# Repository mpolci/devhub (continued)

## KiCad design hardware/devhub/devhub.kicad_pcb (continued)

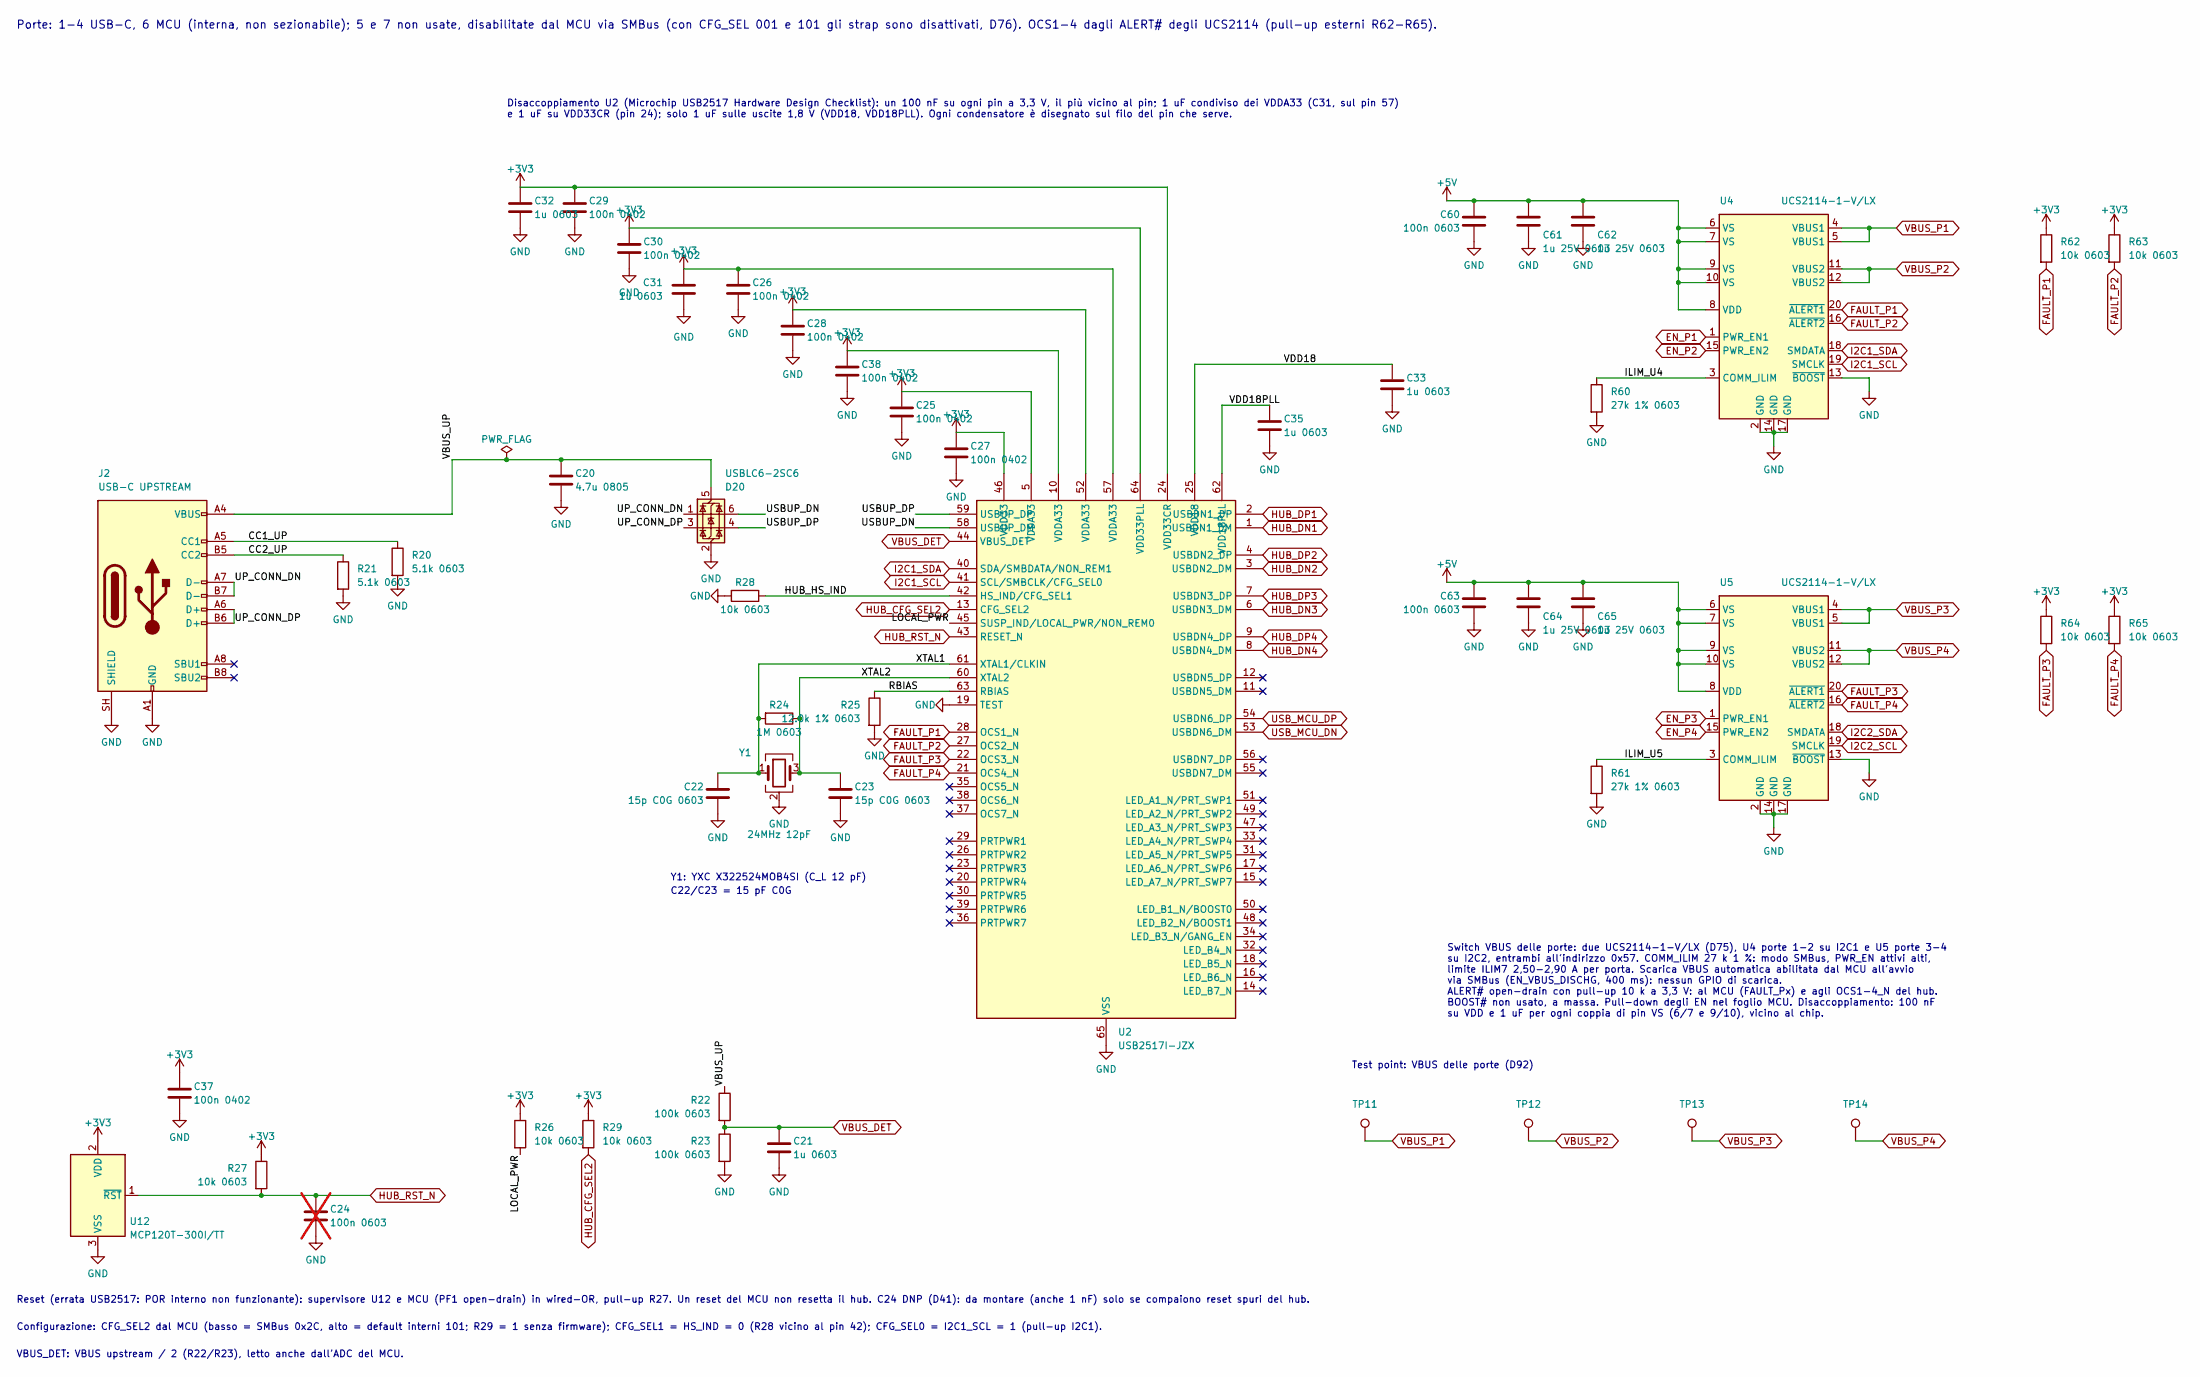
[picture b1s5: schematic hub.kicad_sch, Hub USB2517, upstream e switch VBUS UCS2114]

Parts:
C20: 4.7u 0805; C_0805_2012Metric; MPN lcsc CL21A475KOFNNNE; lcsc C1746
C21, C31, C32, C33, C35: 1u 0603; C_0603_1608Metric; MPN lcsc CL10B105KA8NNNC; lcsc C29936
C22, C23: 15p C0G 0603; C_0603_1608Metric; MPN lcsc CL10C150JB8NNNC; lcsc C1644
C24: 100n 0603; C_0603_1608Metric; MPN lcsc CL10B104KB8NNNC; lcsc C1591; not fitted
C25, C26, C27, C28, C29, C30, C37, C38: 100n 0402; C_0402_1005Metric; MPN lcsc CC0402KRX7R7BB104; lcsc C60474
C60, C63: 100n 0603; C_0603_1608Metric; MPN lcsc CL10B104KB8NNNC; lcsc C1591
C61, C62, C64, C65: 1u 25V 0603; C_0603_1608Metric; MPN lcsc CL10B105KA8NNNC; lcsc C29936
D20: USBLC6-2SC6; SOT-23-6; MPN lcsc USBLC6-2SC6; lcsc C7519
J2: USB-C UPSTREAM; USB_C_Receptacle_GCT_USB4105-xx-A_16P_TopMnt_Horizontal; MPN lcsc USB4105-GF-A; lcsc C3020560
R20, R21: 5.1k 0603; R_0603_1608Metric; MPN lcsc 0603WAF5101T5E; lcsc C23186
R22, R23: 100k 0603; R_0603_1608Metric; MPN lcsc FRC0603F1003TS; lcsc C2906980
R24: 1M 0603; R_0603_1608Metric; MPN lcsc FRC0603F1004TS; lcsc C2907003
R25: 12.0k 1% 0603; R_0603_1608Metric; MPN lcsc RC0603FR-0712KL; lcsc C114659
R26, R27, R28, R29, R62, R63, R64, R65: 10k 0603; R_0603_1608Metric; MPN lcsc FRC0603F1002TS; lcsc C2906982
R60, R61: 27k 1% 0603; R_0603_1608Metric; MPN lcsc RC0603FR-0727KL; lcsc C114614
TP11: VBUS_P1; TestPoint_Pad_D1.5mm
TP12: VBUS_P2; TestPoint_Pad_D1.5mm
TP13: VBUS_P3; TestPoint_Pad_D1.5mm
TP14: VBUS_P4; TestPoint_Pad_D1.5mm
U2: USB2517I-JZX; QFN-64-1EP_9x9mm_P0.5mm_EP4.7x4.7mm_ThermalVias_0.3mm; MPN lcsc USB2517I-JZX; lcsc C478081
U4, U5: UCS2114-1-V/LX; UCS2114_VQFN-20_3x3mm_P0.5mm; MPN lcsc UCS2114-1-V/LX; lcsc C635426
U12: MCP120T-300I/TT; SOT-23; MPN lcsc MCP120T-300I/TT; lcsc C625180
Y1: 24MHz 12pF; Crystal_SMD_3225-4Pin_3.2x2.5mm; MPN lcsc X322524MOB4SI; lcsc C70590

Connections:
+3V3: C25.1, C26.1, C27.1, C28.1, C29.1, C30.1, C31.1, C32.1, C37.1, C38.1, R26.1, R27.1, R29.1, R62.1, R63.1, R64.1, R65.1, U2.5 (VDDA33), U2.10 (VDDA33), U2.24 (VDD33CR), U2.46 (VDD33), U2.52 (VDDA33), U2.57 (VDDA33), U2.64 (VDD33PLL), U12.2 (VDD); also elsewhere on the board
+5V: C60.1, C61.1, C62.1, C63.1, C64.1, C65.1, U4.6 (VS), U4.7 (VS), U4.8 (VDD), U4.9 (VS), U4.10 (VS), U5.6 (VS), U5.7 (VS), U5.8 (VDD), U5.9 (VS), U5.10 (VS); also elsewhere on the board
/Hub USB e switch VBUS/CC1_UP: J2.A5 (CC1), R20.1
/Hub USB e switch VBUS/CC2_UP: J2.B5 (CC2), R21.1
/Hub USB e switch VBUS/HUB_HS_IND: R28.1, U2.42 (HS_IND/CFG_SEL1)
/Hub USB e switch VBUS/ILIM_U4: R60.1, U4.3 (COMM_ILIM)
/Hub USB e switch VBUS/ILIM_U5: R61.1, U5.3 (COMM_ILIM)
/Hub USB e switch VBUS/LOCAL_PWR: R26.2, U2.45 (SUSP_IND/LOCAL_PWR/NON_REM0)
/Hub USB e switch VBUS/RBIAS: R25.1, U2.63 (RBIAS)
/Hub USB e switch VBUS/UP_CONN_DN: D20.1 (I/O1), J2.A7 (D-), J2.B7 (D-)
/Hub USB e switch VBUS/UP_CONN_DP: D20.3 (I/O2), J2.A6 (D+), J2.B6 (D+)
/Hub USB e switch VBUS/USBUP_DN: D20.6 (I/O1), U2.58 (USBUP_DM)
/Hub USB e switch VBUS/USBUP_DP: D20.4 (I/O2), U2.59 (USBUP_DP)
/Hub USB e switch VBUS/VBUS_UP: C20.1, D20.5 (VBUS), J2.A4 (VBUS), J2.A9 (VBUS), J2.B4 (VBUS), J2.B9 (VBUS), R22.1
/Hub USB e switch VBUS/VDD18: C33.1, U2.25 (VDD18)
/Hub USB e switch VBUS/VDD18PLL: C35.1, U2.62 (VDD18PLL)
/Hub USB e switch VBUS/XTAL1: C22.1, R24.2, U2.61 (XTAL1/CLKIN), Y1.1
/Hub USB e switch VBUS/XTAL2: C23.1, R24.1, U2.60 (XTAL2), Y1.3
EN_P1: U4.1 (PWR_EN1); also elsewhere on the board
EN_P2: U4.15 (PWR_EN2); also elsewhere on the board
EN_P3: U5.1 (PWR_EN1); also elsewhere on the board
EN_P4: U5.15 (PWR_EN2); also elsewhere on the board
FAULT_P1: R62.2, U2.28 (OCS1_N), U4.20 (~ALERT1); also elsewhere on the board
FAULT_P2: R63.2, U2.27 (OCS2_N), U4.16 (~ALERT2); also elsewhere on the board
FAULT_P3: R64.2, U2.22 (OCS3_N), U5.20 (~ALERT1); also elsewhere on the board
FAULT_P4: R65.2, U2.21 (OCS4_N), U5.16 (~ALERT2); also elsewhere on the board
GND: C20.2, C21.2, C22.2, C23.2, C24.2, C25.2, C26.2, C27.2, C28.2, C29.2, C30.2, C31.2, C32.2, C33.2, C35.2, C37.2, C38.2, C60.2, C61.2, C62.2, C63.2, C64.2, C65.2, D20.2 (GND), J2.A1 (GND), J2.A12 (GND), J2.B1 (GND), J2.B12 (GND), J2.SH (SHIELD), R20.2, R21.2, R23.2, R25.2, R28.2, R60.2, R61.2, U2.19 (TEST), U2.65 (VSS), U4.2 (GND), U4.13 (~BOOST), U4.14 (GND), U4.17 (GND), U5.2 (GND), U5.13 (~BOOST), U5.14 (GND), U5.17 (GND), U12.3 (VSS), Y1.2 (G), Y1.4 (G); also elsewhere on the board
HUB_CFG_SEL2: R29.2, U2.13 (CFG_SEL2); also elsewhere on the board
HUB_DN1: U2.1 (USBDN1_DM); also elsewhere on the board
HUB_DN2: U2.3 (USBDN2_DM); also elsewhere on the board
HUB_DN3: U2.6 (USBDN3_DM); also elsewhere on the board
HUB_DN4: U2.8 (USBDN4_DM); also elsewhere on the board
HUB_DP1: U2.2 (USBDN1_DP); also elsewhere on the board
HUB_DP2: U2.4 (USBDN2_DP); also elsewhere on the board
HUB_DP3: U2.7 (USBDN3_DP); also elsewhere on the board
HUB_DP4: U2.9 (USBDN4_DP); also elsewhere on the board
HUB_RST_N: C24.1, R27.2, U2.43 (RESET_N), U12.1 (~RST); also elsewhere on the board
I2C1_SCL: U2.41 (SCL/SMBCLK/CFG_SEL0), U4.19 (SMCLK); also elsewhere on the board
I2C1_SDA: U2.40 (SDA/SMBDATA/NON_REM1), U4.18 (SMDATA); also elsewhere on the board
I2C2_SCL: U5.19 (SMCLK); also elsewhere on the board
I2C2_SDA: U5.18 (SMDATA); also elsewhere on the board
USB_MCU_DN: U2.53 (USBDN6_DM); also elsewhere on the board
USB_MCU_DP: U2.54 (USBDN6_DP); also elsewhere on the board
VBUS_DET: C21.1, R22.2, R23.1, U2.44 (VBUS_DET); also elsewhere on the board
VBUS_P1: TP11.1 (1_1), U4.4 (VBUS1), U4.5 (VBUS1); also elsewhere on the board
VBUS_P2: TP12.1 (1_1), U4.11 (VBUS2), U4.12 (VBUS2); also elsewhere on the board
VBUS_P3: TP13.1 (1_1), U5.4 (VBUS1), U5.5 (VBUS1); also elsewhere on the board
VBUS_P4: TP14.1 (1_1), U5.11 (VBUS2), U5.12 (VBUS2); also elsewhere on the board

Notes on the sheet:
Y1: YXC X322524MOB4SI (C_L 12 pF)
C22/C23 = 15 pF C0G
Test point: VBUS delle porte (D92)
Disaccoppiamento U2 (Microchip USB2517 Hardware Design Checklist): un 100 nF su ogni pin a 3,3 V, il più vicino al pin; 1 uF condiviso dei VDDA33 (C31, sul pin 57) e 1 uF su VDD33CR (pin 24); solo 1 uF sulle uscite 1,8 V (VDD18, VDD18PLL). Ogni condensatore è disegnato sul filo del pin che serve.
VBUS_DET: VBUS upstream / 2 (R22/R23), letto anche dall'ADC del MCU.
Reset (errata USB2517: POR interno non funzionante): supervisore U12 e MCU (PF1 open-drain) in wired-OR, pull-up R27. Un reset del MCU non resetta il hub. C24 DNP (D41): da montare (anche 1 nF) solo se compaiono reset spuri del hub.
Configurazione: CFG_SEL2 dal MCU (basso = SMBus 0x2C, alto = default interni 101; R29 = 1 senza firmware); CFG_SEL1 = HS_IND = 0 (R28 vicino al pin 42); CFG_SEL0 = I2C1_SCL = 1 (pull-up I2C1).
Switch VBUS delle porte: due UCS2114-1-V/LX (D75), U4 porte 1-2 su I2C1 e U5 porte 3-4 su I2C2, entrambi all'indirizzo 0x57. COMM_ILIM 27 k 1 %: modo SMBus, PWR_EN attivi alti, limite ILIM7 2,50-2,90 A per porta. Scarica VBUS automatica abilitata dal MCU all'avvio via SMBus (EN_VBUS_DISCHG, 400 ms)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
Porte: 1-4 USB-C, 6 MCU (interna, non sezionabile); 5 e 7 non usate, disabilitate dal MCU via SMBus (con CFG_SEL 001 e 101 gli strap sono disattivati, D76). OCS1-4 dagli ALERT# degli UCS2114 (pull-up esterni R62-R65).

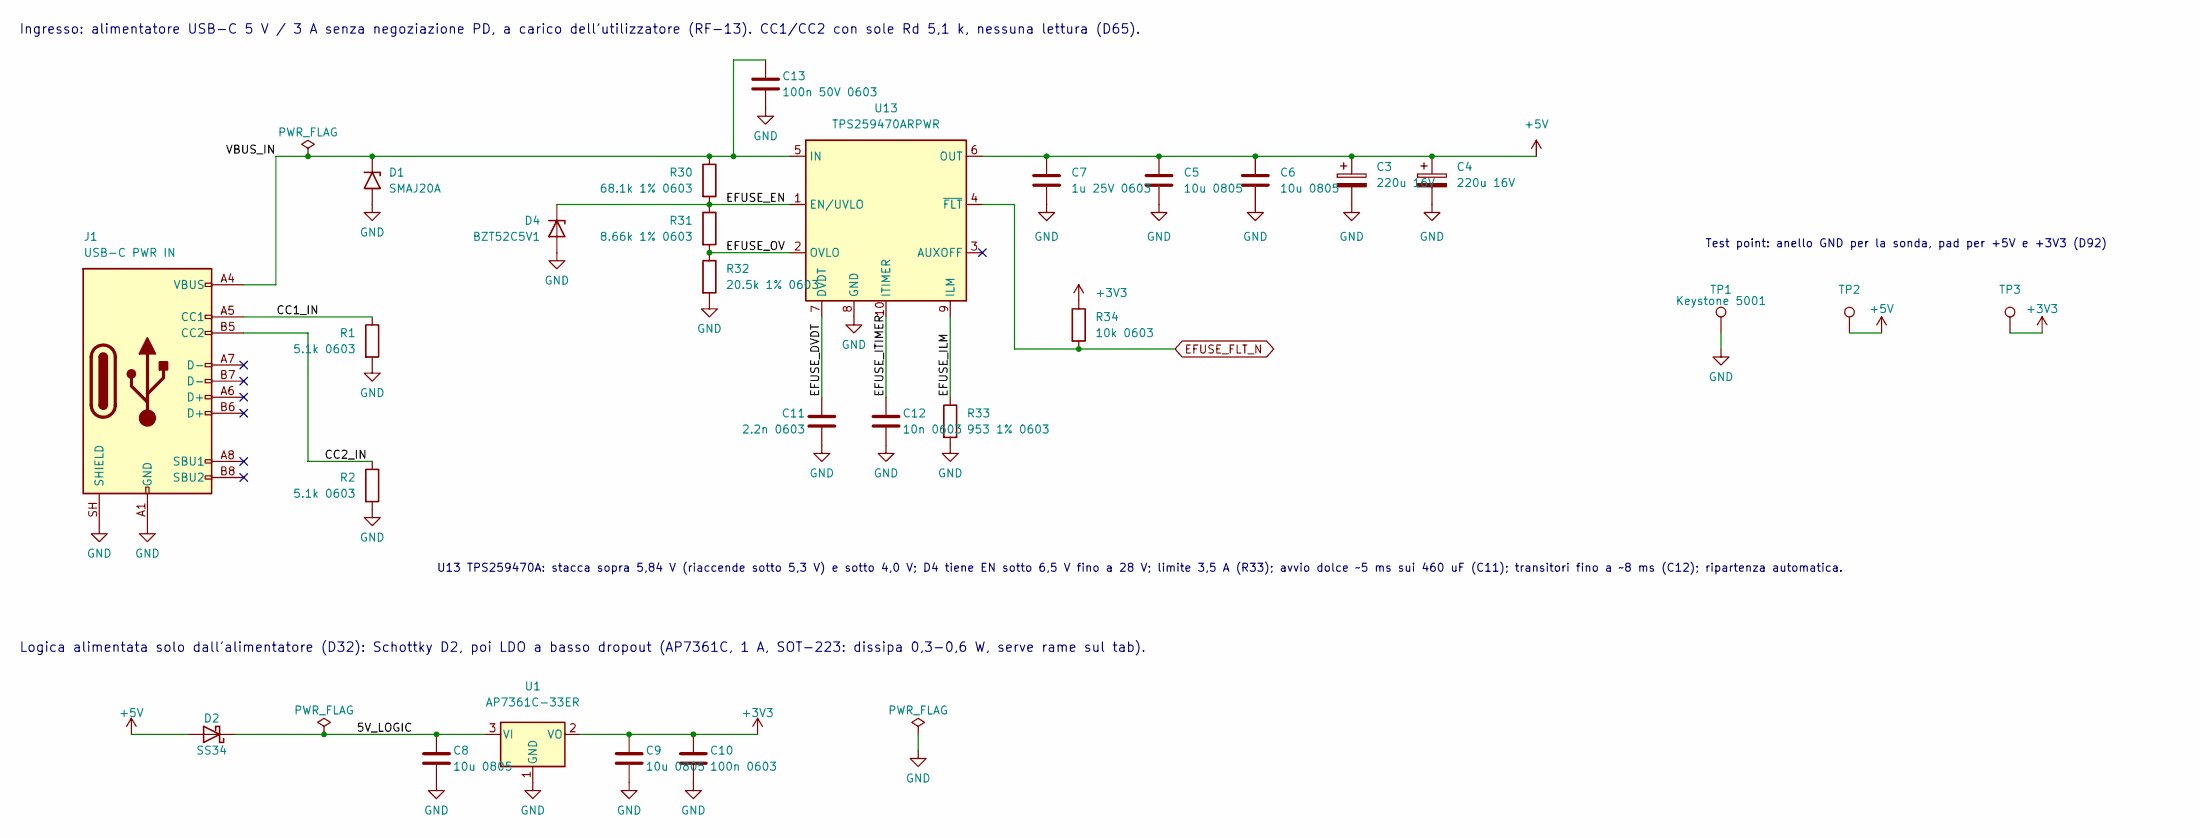
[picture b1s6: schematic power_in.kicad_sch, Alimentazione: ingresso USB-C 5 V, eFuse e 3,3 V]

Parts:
C3, C4: 220u 16V; CP_Elec_6.3x7.7; MPN lcsc EEE-FK1C221XP; lcsc C128533
C5, C6, C8, C9: 10u 0805; C_0805_2012Metric; MPN lcsc GRM21BR61H106KE43L; lcsc C440198
C7: 1u 25V 0603; C_0603_1608Metric; MPN lcsc CL10B105KA8NNNC; lcsc C29936
C10: 100n 0603; C_0603_1608Metric; MPN lcsc CL10B104KB8NNNC; lcsc C1591
C11: 2.2n 0603; C_0603_1608Metric; MPN lcsc CL10B222KB8NNNC; lcsc C16033
C12: 10n 0603; C_0603_1608Metric; MPN lcsc CL10B103KB8NNNC; lcsc C1589
C13: 100n 50V 0603; C_0603_1608Metric; MPN lcsc CL10B104KB8NNNC; lcsc C1591
D1: SMAJ20A; D_SMA; MPN lcsc SMAJ20A-13-F; lcsc C134969
D2: SS34; D_SMA; MPN lcsc B340A-13-F; lcsc C85098
D4: BZT52C5V1; D_SOD-123; MPN lcsc BZT52C5V1-7-F; lcsc C151588
J1: USB-C PWR IN; USB_C_Receptacle_GCT_USB4105-xx-A_16P_TopMnt_Horizontal; MPN lcsc USB4105-GF-A; lcsc C3020560
R1, R2: 5.1k 0603; R_0603_1608Metric; MPN lcsc 0603WAF5101T5E; lcsc C23186
R30: 68.1k 1% 0603; R_0603_1608Metric; MPN lcsc RC0603FR-0768K1L; lcsc C185315
R31: 8.66k 1% 0603; R_0603_1608Metric; MPN lcsc 0603WAF8661T5E; lcsc C23114
R32: 20.5k 1% 0603; R_0603_1608Metric; MPN lcsc RC0603FR-0720K5L; lcsc C273789
R33: 953 1% 0603; R_0603_1608Metric; MPN lcsc RC0603FR-07953RL; lcsc C137668
R34: 10k 0603; R_0603_1608Metric; MPN lcsc FRC0603F1002TS; lcsc C2906982
TP1: Keystone 5001; TestPoint_Keystone_5000-5004_Miniature; MPN mouser 5001; lcsc C238122
TP2: +5V; TestPoint_Pad_D1.5mm
TP3: +3V3; TestPoint_Pad_D1.5mm
U1: AP7361C-33ER; SOT-223-3_TabPin2; MPN lcsc AP7361C-33ER-13; lcsc C3743528
U13: TPS259470ARPWR; C3662799_VQFN-10_L2_0-W2_0-P0_45-TL; MPN lcsc TPS259470ARPWR; lcsc C3662799

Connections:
+3V3: C9.1, C10.1, R34.1, TP3.1 (1_1), U1.2 (VO); also elsewhere on the board
+5V: C3.1, C4.1, C5.1, C6.1, C7.1, D2.2 (A), TP2.1 (1_1), U13.6 (OUT); also elsewhere on the board
/Alimentazione/5V_LOGIC: C8.1, D2.1 (K), U1.3 (VI)
/Alimentazione/CC1_IN: J1.A5 (CC1), R1.1
/Alimentazione/CC2_IN: J1.B5 (CC2), R2.1
/Alimentazione/EFUSE_DVDT: C11.1, U13.7 (DVDT)
/Alimentazione/EFUSE_EN: D4.1 (K), R30.2, R31.1, U13.1 (EN/UVLO)
/Alimentazione/EFUSE_ILM: R33.1, U13.9 (ILM)
/Alimentazione/EFUSE_ITIMER: C12.1, U13.10 (ITIMER)
/Alimentazione/EFUSE_OV: R31.2, R32.1, U13.2 (OVLO)
/Alimentazione/VBUS_IN: C13.1, D1.1 (K), J1.A4 (VBUS), J1.A9 (VBUS), J1.B4 (VBUS), J1.B9 (VBUS), R30.1, U13.5 (IN)
EFUSE_FLT_N: R34.2, U13.4 (~FLT); also elsewhere on the board
GND: C3.2, C4.2, C5.2, C6.2, C7.2, C8.2, C9.2, C10.2, C11.2, C12.2, C13.2, D1.2 (A), D4.2 (A), J1.A1 (GND), J1.A12 (GND), J1.B1 (GND), J1.B12 (GND), J1.SH (SHIELD), R1.2, R2.2, R32.2, R33.2, TP1.1 (1_1), U1.1 (GND), U13.8 (GND); also elsewhere on the board

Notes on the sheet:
U13 TPS259470A: stacca sopra 5,84 V (riaccende sotto 5,3 V) e sotto 4,0 V; D4 tiene EN sotto 6,5 V fino a 28 V; limite 3,5 A (R33); avvio dolce ~5 ms sui 460 uF (C11); transitori fino a ~8 ms (C12); ripartenza automatica.
Ingresso: alimentatore USB-C 5 V / 3 A senza negoziazione PD, a carico dell'utilizzatore (RF-13). CC1/CC2 con sole Rd 5,1 k, nessuna lettura (D65).
Test point: anello GND per la sonda, pad per +5V e +3V3 (D92)
Logica alimentata solo dall'alimentatore (D32): Schottky D2, poi LDO a basso dropout (AP7361C, 1 A, SOT-223: dissipa 0,3-0,6 W, serve rame sul tab).

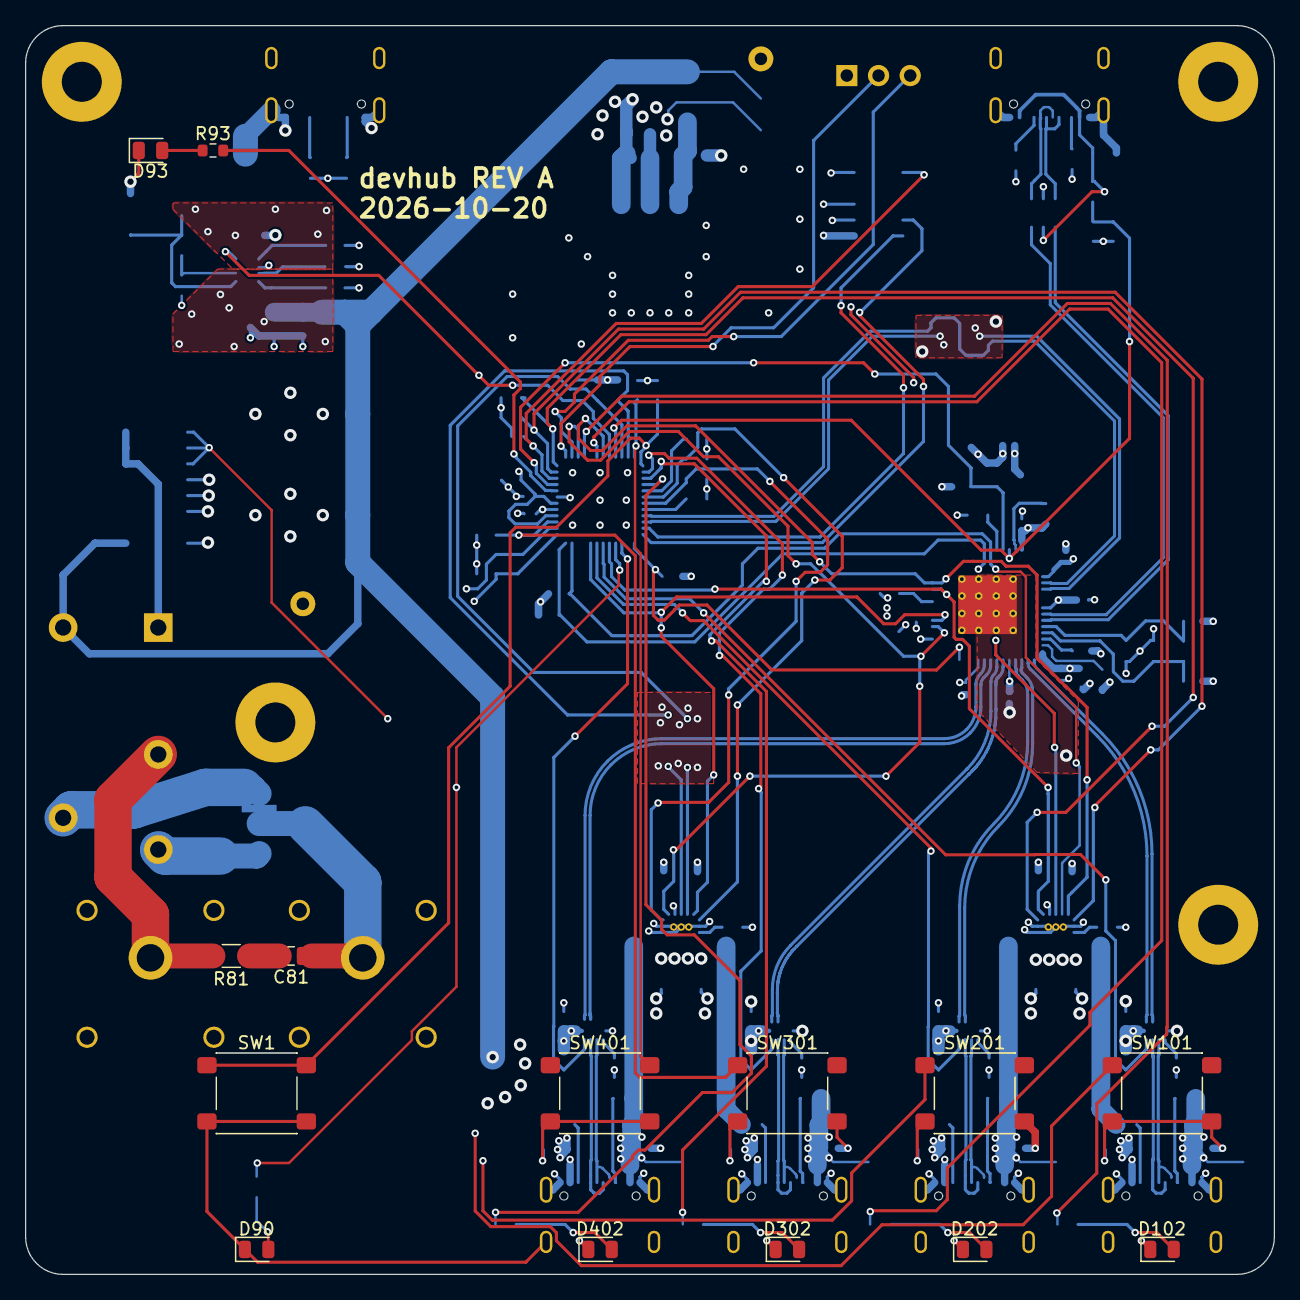
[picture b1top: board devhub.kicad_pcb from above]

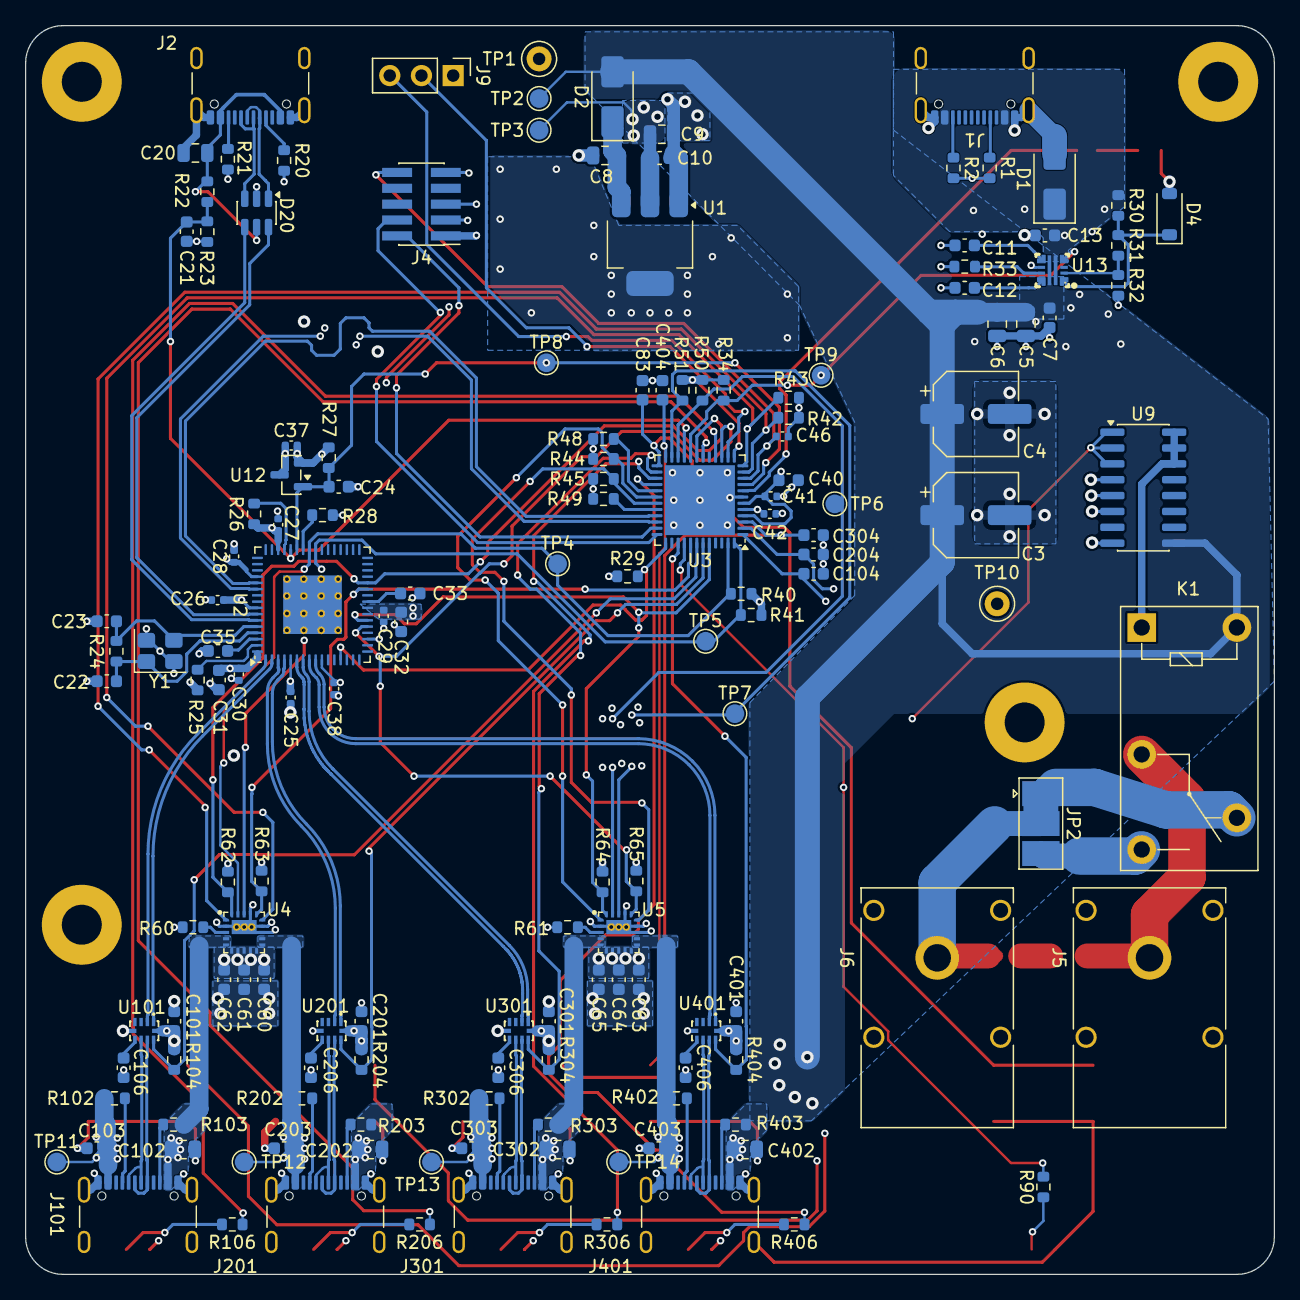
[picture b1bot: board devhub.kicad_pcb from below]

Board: 4 copper layers, 100.0 x 100.0 mm, 170 parts (152 on the bottom side), 112 nets.

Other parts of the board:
H1, H2, H3, H4: M3; MountingHole_3.2mm_M3_Pad

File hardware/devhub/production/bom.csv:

Designator,Footprint,Quantity,Value,LCSC Part #
"C10, C101, C103, C104, C201, C203, C204, C24, C301, C303, C304, C401, C403, C404, C60, C63, C83",0603,17,100n 0603,
"C102, C202, C302, C402",0805,4,22u 10V 0805,
"C106, C206, C306, C406, C61, C62, C64, C65, C7",0603,9,1u 25V 0603,
C11,0603,1,2.2n 0603,
C12,0603,1,10n 0603,
C13,0603,1,100n 50V 0603,
C20,0805,1,4.7u 0805,
"C21, C31, C32, C33, C35",0603,5,1u 0603,
"C22, C23",0603,2,15p C0G 0603,
"C25, C26, C27, C28, C29, C30, C37, C38, C41, C42, C46",0402,11,100n 0402,
"C3, C4",CP_Elec_6.3x7.7,2,220u 16V,
C40,0603,1,4.7u 0603,
"C5, C6, C8, C9",0805,4,10u 0805,
C81,0805,1,100n 50V 0805 DNP,
D1,D_SMA,1,SMAJ20A,
"D102, D202, D302, D402, D90",0805,5,verde 0805,
D2,D_SMA,1,SS34,
D20,SOT-23-6,1,USBLC6-2SC6,
D4,D_SOD-123,1,BZT52C5V1,
D93,0805,1,arancio 0805,
J1,USB_C_Receptacle_GCT_USB4105-xx-A_16P_TopMnt_Horizontal,1,USB-C PWR IN,
"J101, J201, J301, J401",USB_C_Receptacle_GCT_USB4105-xx-A_16P_TopMnt_Horizontal,4,USB-C,
J2,USB_C_Receptacle_GCT_USB4105-xx-A_16P_TopMnt_Horizontal,1,USB-C UPSTREAM,
J4,PinHeader_2x05_P1.27mm_Vertical_SMD,1,SWD,
J5,Banana_Cliff_FCR7350B_S16N-PC_Horizontal,1,Banana COM 1,
J6,Banana_Cliff_FCR7350R_S16N-PC_Horizontal,1,Banana NC 1,
JP2,SolderJumper-3_P2.4mm_Bridged12_Pad2.0x3.0mm,1,NC/NO,
K1,Relay_SPDT_Omron-G5Q-1,1,G5Q-1 DC5,
"R1, R2, R20, R21",0603,4,5.1k 0603,
"R102, R103, R202, R203, R302, R303, R402, R403",0603,8,56k 0603,
"R104, R204, R22, R23, R304, R404",0603,6,100k 0603,
"R106, R206, R306, R406, R90, R93",0603,6,1k 0603,
R24,0603,1,1M 0603,
R25,0603,1,12.0k 1% 0603,
"R26, R27, R28, R29, R34, R42, R43, R44, R45, R48, R49, R62, R63, R64, R65",0603,15,10k 0603,
R30,0603,1,68.1k 1% 0603,
R31,0603,1,8.66k 1% 0603,
R32,0603,1,20.5k 1% 0603,
R33,0603,1,953 1% 0603,
"R40, R41, R50, R51",0603,4,4.7k 0603,
"R60, R61",0603,2,27k 1% 0603,
R81,1206,1,100 0.25W 1206 DNP,
"SW1, SW101, SW201, SW301, SW401",SW_SPST_PTS645Sx43SMTR92,5,"Push button switch, generic, two pins",
"TP1, TP10",TestPoint_Keystone_5000-5004_Miniature,2,Keystone 5001,
U1,SOT-223-3_TabPin2,1,AP7361C-33ER,
"U101, U201, U301, U401",C3657361_UQFN-10_L2_0-W1_5-P0_50-TL,4,PI3USB4002A,
U12,SOT-23,1,MCP120T-300I/TT,
U13,C3662799_VQFN-10_L2_0-W2_0-P0_45-TL,1,TPS259470ARPWR,
U2,QFN-64-1EP_9x9mm_P0.5mm_EP4.7x4.7mm_ThermalVias_0.3mm,1,USB2517I-JZX,
U3,QFN-48-1EP_7x7mm_P0.5mm_EP5.6x5.6mm,1,STM32G0B1CEU6,
"U4, U5",UCS2114_VQFN-20_3x3mm_P0.5mm,2,UCS2114-1-V/LX,
U9,SOIC-16_3.9x9.9mm_P1.27mm,1,ULN2003V12,
Y1,Crystal_SMD_3225-4Pin_3.2x2.5mm,1,24MHz 12pF,

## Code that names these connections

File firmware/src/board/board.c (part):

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static const pin_t PIN_FAULT[BOARD_N_PORTS] = {PIN(B, 0), PIN(D, 3), PIN(B, 5), PIN(A, 4)};
static const pin_t PIN_LED[BOARD_N_PORTS] = {PIN(A, 5), PIN(A, 7), PIN(B, 15), PIN(A, 8)};
static const pin_t PIN_BTN[BOARD_N_BUTTONS] = {PIN(C, 13), PIN(C, 14), PIN(C, 15), PIN(B, 12), PIN(B, 13)};
static const pin_t PIN_LED_HOST = PIN(F, 0);
static const pin_t PIN_HUB_RST_N = PIN(F, 1);
static const pin_t PIN_HUB_CFG_SEL2 = PIN(A, 15);
static const pin_t PIN_RLY1 = PIN(D, 2);
static const pin_t PIN_EFUSE_FLT_N = PIN(B, 1);
static const pin_t PIN_I2C1_SCL = PIN(B, 8);

#define VBUS_DET_ADC_CHANNEL 10 // PB2
#define TEMP_ADC_CHANNEL 12     // internal temperature sensor
#define VREFINT_ADC_CHANNEL 13  // internal voltage reference
#define VBUS_DET_DIVIDER 2
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    __HAL_RCC_SYSCFG_CLK_ENABLE();
    __HAL_RCC_PWR_CLK_ENABLE();

    // Remove the UCPD dead-battery pull-downs (Rd) from PA8, PB15, PD0, PD2
    // before those pins are driven (RM0444 SYSCFG_CFGR1, docs/pinout-mcu.md).
    SYSCFG->CFGR1 |= SYSCFG_CFGR1_UCPD1_STROBE | SYSCFG_CFGR1_UCPD2_STROBE;

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        pin_output(PIN_EN[i], false, GPIO_MODE_OUTPUT_PP);
        pin_output(PIN_OE_N[i], true, GPIO_MODE_OUTPUT_PP);
    }
    pin_output(PIN_RLY1, false, GPIO_MODE_OUTPUT_PP);

    for (uint8_t i = 0; i < BOARD_N_PORTS; i++) {
        pin_output(PIN_LED[i], false, GPIO_MODE_OUTPUT_PP);
    }
    pin_output(PIN_LED_HOST, false, GPIO_MODE_OUTPUT_PP);

    // Hub control: reset line released (open-drain, never push-pull), CFG_SEL2
    // left to its pull-up until hub_ctrl decides.
    pin_output(PIN_HUB_RST_N, true, GPIO_MODE_OUTPUT_OD);
    pin_mode(PIN_HUB_CFG_SEL2, GPIO_MODE_INPUT, GPIO_NOPULL);

    for (uint8_t i = 0; i < BOARD_N_BUTTONS; i++) {
        pin_mode(PIN_BTN[i], GPIO_MODE_INPUT, GPIO_PULLUP);
    }

    // Fault inputs have external pull-ups. PA4 may carry a pull-down left by
    // the ROM bootloader: configuring it with no pull removes it.
    for (uint8_t i = 0; i < BOARD_N_PORTS; i++) {
        pin_mode(PIN_FAULT[i], GPIO_MODE_IT_FALLING, GPIO_NOPULL);
    }
    pin_mode(PIN_EFUSE_FLT_N, GPIO_MODE_INPUT, GPIO_NOPULL);

    // VBUS_DET: analog input on PB2.
    pin_mode((pin_t)PIN(B, 2), GPIO_MODE_ANALOG, GPIO_NOPULL);
    adc_init();

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}

void board_led_host(bool on) {
    pin_write(PIN_LED_HOST, on);
}

void board_relay(bool energized) {
    pin_write(PIN_RLY1, energized);
}

bool board_relay_get(void) {
    return pin_out_state(PIN_RLY1);
}

bool board_button(uint8_t idx) {
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}

bool board_efuse_fault(void) {
    return !pin_read(PIN_EFUSE_FLT_N);
}

void board_hub_reset_drive(bool low) {
    pin_write(PIN_HUB_RST_N, !low);
}

bool board_hub_reset_level(void) {
    return pin_read(PIN_HUB_RST_N);
}

void board_hub_cfg_sel2(bool high) {
    pin_output(PIN_HUB_CFG_SEL2, high, GPIO_MODE_OUTPUT_PP);
}

bool board_i2c1_scl_level(void) {
    return pin_read(PIN_I2C1_SCL);
}

uint16_t board_vbus_det_mv(void) {
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        PIN_OE_N[i].port->BSRR = PIN_OE_N[i].pin;
        PIN_EN[i].port->BRR = PIN_EN[i].pin;
    }
    PIN_RLY1.port->BRR = PIN_RLY1.pin;
    for (;;) {
    }
}
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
